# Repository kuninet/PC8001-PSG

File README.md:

# PC8001-PSG (GSX8800風PSG音源ボード)

## 概要

* PC-8001用のPSGを2個搭載したボードです。
* I/OアドレスはGSX8800風(0A0h-0A3h or 0A4h-0A7h)にしてます。

  |I/Oアドレス|説明|
  |:--|:--|
  |0A0h(0A4h)|PSG#1 レジスタ番号|
  |0A1h(0A5h)|PSG#1 データ|
  |0A2h(0A6h)|PSG#2 レジスタ番号|
  |0A3h(0A7h)|PSG#2 データ|

## 回路図

## ジャンパ設定

* I/Oアドレスを変更することが可能です。

  |JP|1-2|2-3|
  |:--|:--|:--|
  |JP1(PSG#1)|0A0h-0A1h|0A4h-0A5h|
  |JP2(PSG#2)|0A2h-0A3h|0A6h-0A7h|

## 部品表

[KiCad/PC8001-PSG.csv](KiCad/PC8001-PSG.csv)

## 参考URL

* https://piclabo.blog.ss-blog.jp/Simple8Z_PSG
  * SuperSimpleController（その２１）PSG(AY-3-8910A)の動作確認

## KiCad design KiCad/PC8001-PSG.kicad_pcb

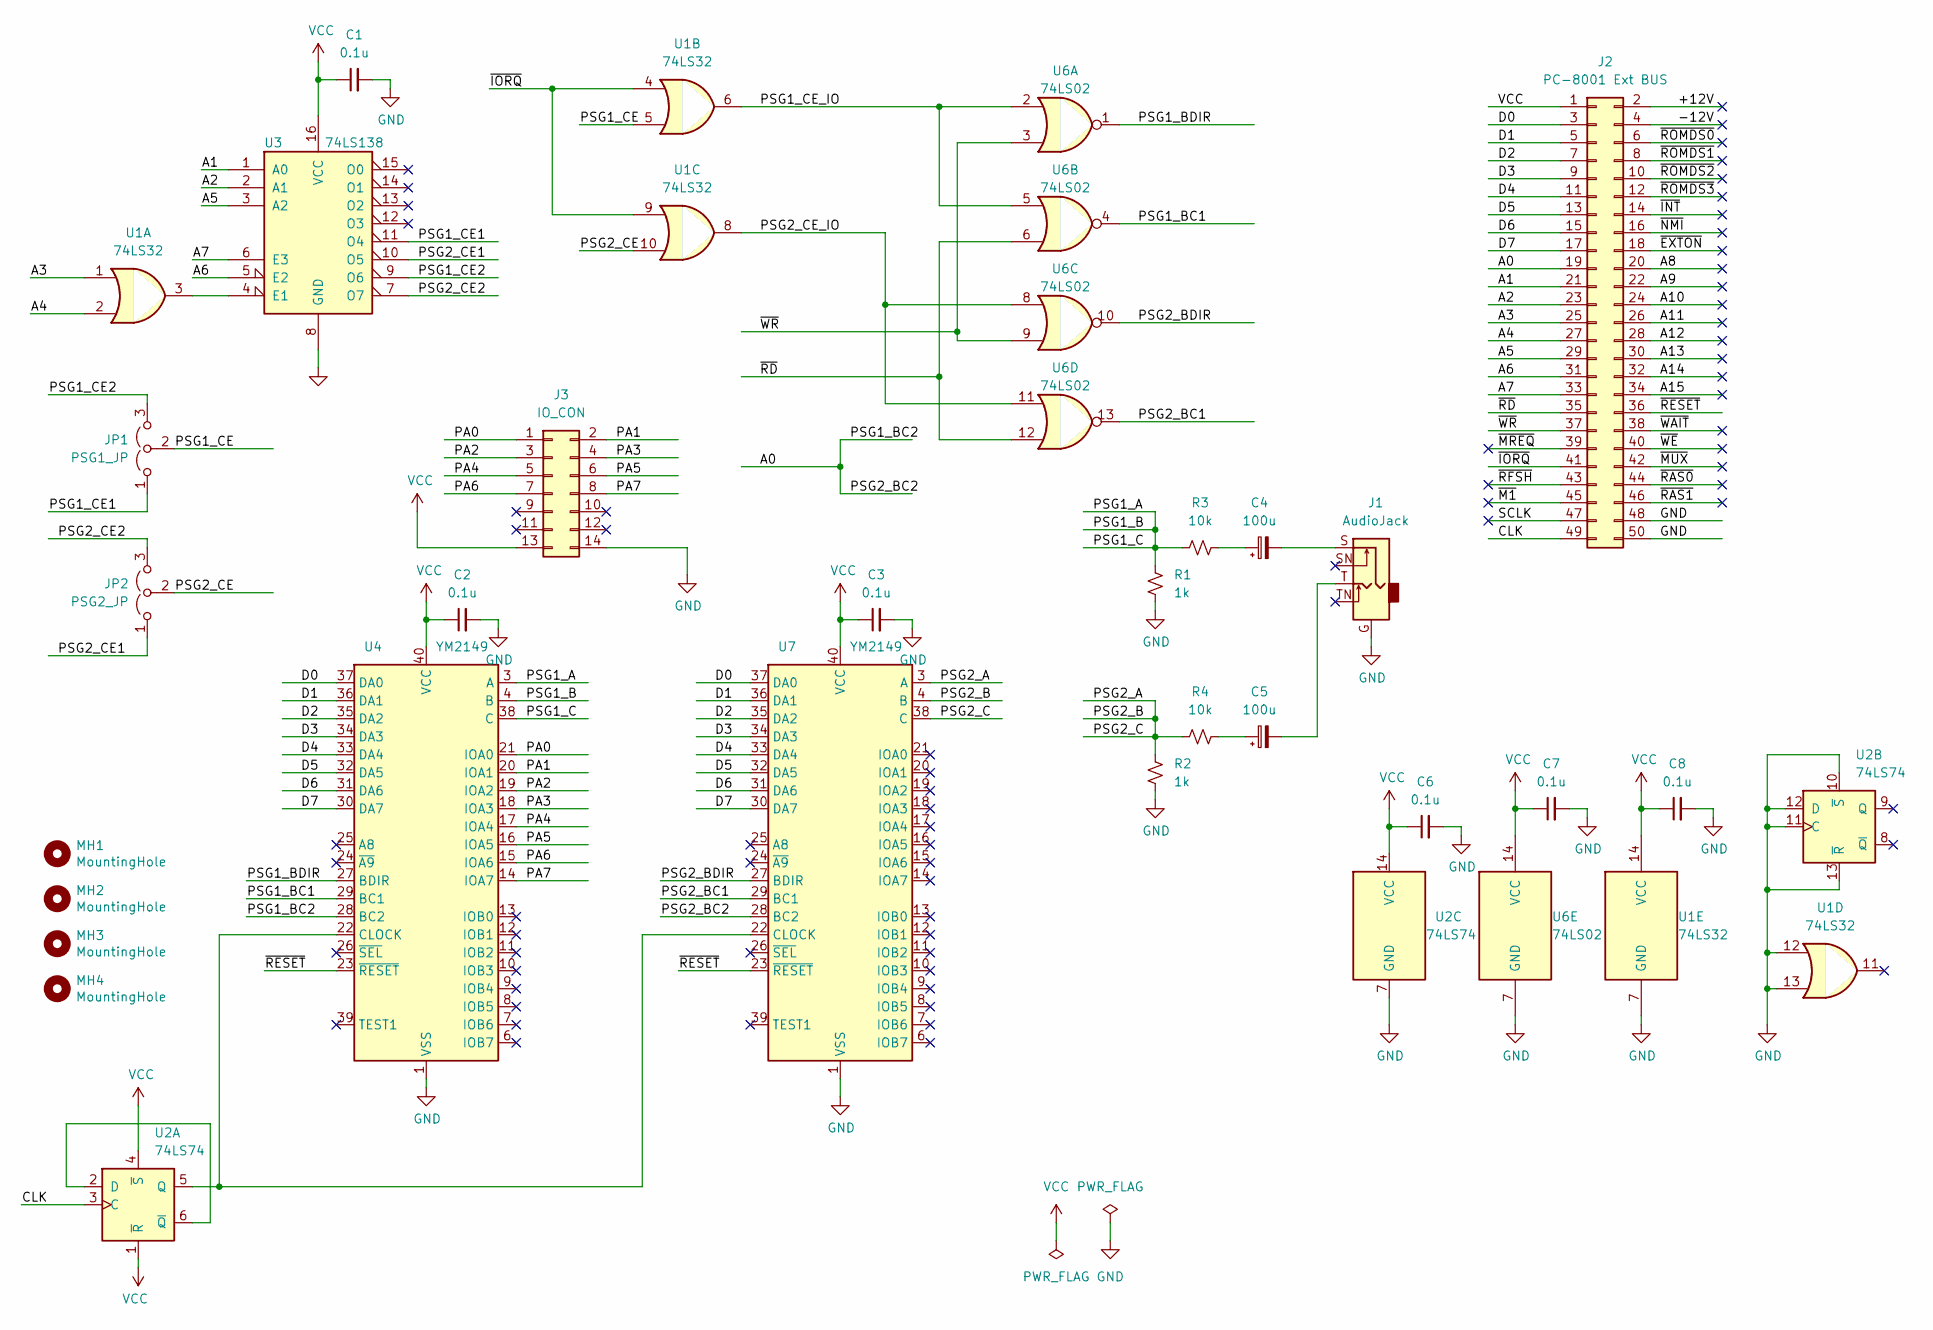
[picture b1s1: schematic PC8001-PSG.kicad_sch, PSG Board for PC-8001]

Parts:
C1, C2, C3, C6, C7, C8: 0.1u; C_Disc_D3.0mm_W1.6mm_P2.50mm
C4, C5: 100u; CP_Radial_D5.0mm_P2.50mm
J1: AudioJack; AJ-1780-2
J2: PC-8001 Ext BUS; PinHeader_2x25_P2.54mm_Horizontal
J3: IO_CON; PinHeader_2x07_P2.54mm_Vertical
JP1: PSG1_JP; PinHeader_1x03_P2.54mm_Vertical
JP2: PSG2_JP; PinHeader_1x03_P2.54mm_Vertical
MH1, MH2, MH3, MH4: MountingHole; MountingHole_3.2mm_M3
R1, R2: 1k; R_Axial_DIN0207_L6.3mm_D2.5mm_P10.16mm_Horizontal
R3, R4: 10k; R_Axial_DIN0207_L6.3mm_D2.5mm_P10.16mm_Horizontal
U1: 74LS32; DIP-14_W7.62mm_Socket
U2: 74LS74; DIP-14_W7.62mm_Socket
U3: 74LS138; DIP-16_W7.62mm_Socket
U4, U7: YM2149; DIP-40_W15.24mm
U6: 74LS02; DIP-14_W7.62mm_Socket

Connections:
/+12V: J2.2
/-12V: J2.4
/A0: J2.19, U4.28 (BC2), U7.28 (BC2)
/A1: J2.21, U3.1 (A0)
/A2: J2.23, U3.2 (A1)
/A3: J2.25, U1.1
/A4: J2.27, U1.2
/A5: J2.29, U3.3 (A2)
/A6: J2.31, U3.5 (E2)
/A7: J2.33, U3.6 (E3)
/A8: J2.20
/A9: J2.22
/A10: J2.24
/A11: J2.26
/A12: J2.28
/A13: J2.30
/A14: J2.32
/A15: J2.34
/CLK: J2.49, U2.3 (C)
/D0: J2.3, U4.37 (DA0), U7.37 (DA0)
/D1: J2.5, U4.36 (DA1), U7.36 (DA1)
/D2: J2.7, U4.35 (DA2), U7.35 (DA2)
/D3: J2.9, U4.34 (DA3), U7.34 (DA3)
/D4: J2.11, U4.33 (DA4), U7.33 (DA4)
/D5: J2.13, U4.32 (DA5), U7.32 (DA5)
/D6: J2.15, U4.31 (DA6), U7.31 (DA6)
/D7: J2.17, U4.30 (DA7), U7.30 (DA7)
/PA0: J3.1, U4.21 (IOA0)
/PA1: J3.2, U4.20 (IOA1)
/PA2: J3.3, U4.19 (IOA2)
/PA3: J3.4, U4.18 (IOA3)
/PA4: J3.5, U4.17 (IOA4)
/PA5: J3.6, U4.16 (IOA5)
/PA6: J3.7, U4.15 (IOA6)
/PA7: J3.8, U4.14 (IOA7)
/PSG1_A: R1.2, R3.1, U4.3 (A), U4.4 (B), U4.38 (C)
/PSG1_BC1: U4.29 (BC1), U6.4
/PSG1_BDIR: U4.27 (BDIR), U6.1
/PSG1_CE: JP1.2 (C), U1.5
/PSG1_CE1: JP1.1 (A), U3.11 (O4)
/PSG1_CE2: JP1.3 (B), U3.9 (O6)
/PSG1_CE_IO: U1.6, U6.2, U6.5
/PSG2_A: R2.2, R4.1, U7.3 (A), U7.4 (B), U7.38 (C)
/PSG2_BC1: U6.13, U7.29 (BC1)
/PSG2_BDIR: U6.10, U7.27 (BDIR)
/PSG2_CE: JP2.2 (C), U1.10
/PSG2_CE1: JP2.1 (A), U3.10 (O5)
/PSG2_CE2: JP2.3 (B), U3.7 (O7)
/PSG2_CE_IO: U1.8, U6.8, U6.11
/SCLK: J2.47
/~EXTON: J2.18
/~INT: J2.14
/~IORQ: J2.41, U1.4, U1.9
/~M1: J2.45
/~MREQ: J2.39
/~MUX: J2.42
/~NMI: J2.16
/~RAS0: J2.44
/~RAS1: J2.46
/~RD: J2.35, U6.6, U6.12
/~RESET: J2.36, U4.23 (~RESET), U7.23 (~RESET)
/~RFSH: J2.43
/~ROMDS0: J2.6
/~ROMDS1: J2.8
/~ROMDS2: J2.10
/~ROMDS3: J2.12
/~WAIT: J2.38
/~WE: J2.40
/~WR: J2.37, U6.3, U6.9
GND: C1.2, C2.2, C3.2, C6.2, C7.2, C8.2, J1.G, J2.48, J2.50, J3.14, R1.1, R2.1, U1.7 (GND), U1.12, U1.13, U2.7 (GND), U2.10 (~S), U2.11 (C), U2.12 (D), U2.13 (~R), U3.8 (GND), U4.1 (VSS), U6.7 (GND), U7.1 (VSS)
unnamed: C4.1, R3.2
unnamed: C4.2, J1.S
unnamed: C5.1, R4.2
unnamed: C5.2, J1.T
unnamed: U2.2 (D), U2.6 (~Q)
unnamed: U2.5 (Q), U4.22 (CLOCK), U7.22 (CLOCK)
unnamed: U1.3, U3.4 (E1)
VCC: C1.1, C2.1, C3.1, C6.1, C7.1, C8.1, J2.1, J3.13, U1.14 (VCC), U2.1 (~R), U2.4 (~S), U2.14 (VCC), U3.16 (VCC), U4.40 (VCC), U6.14 (VCC), U7.40 (VCC)

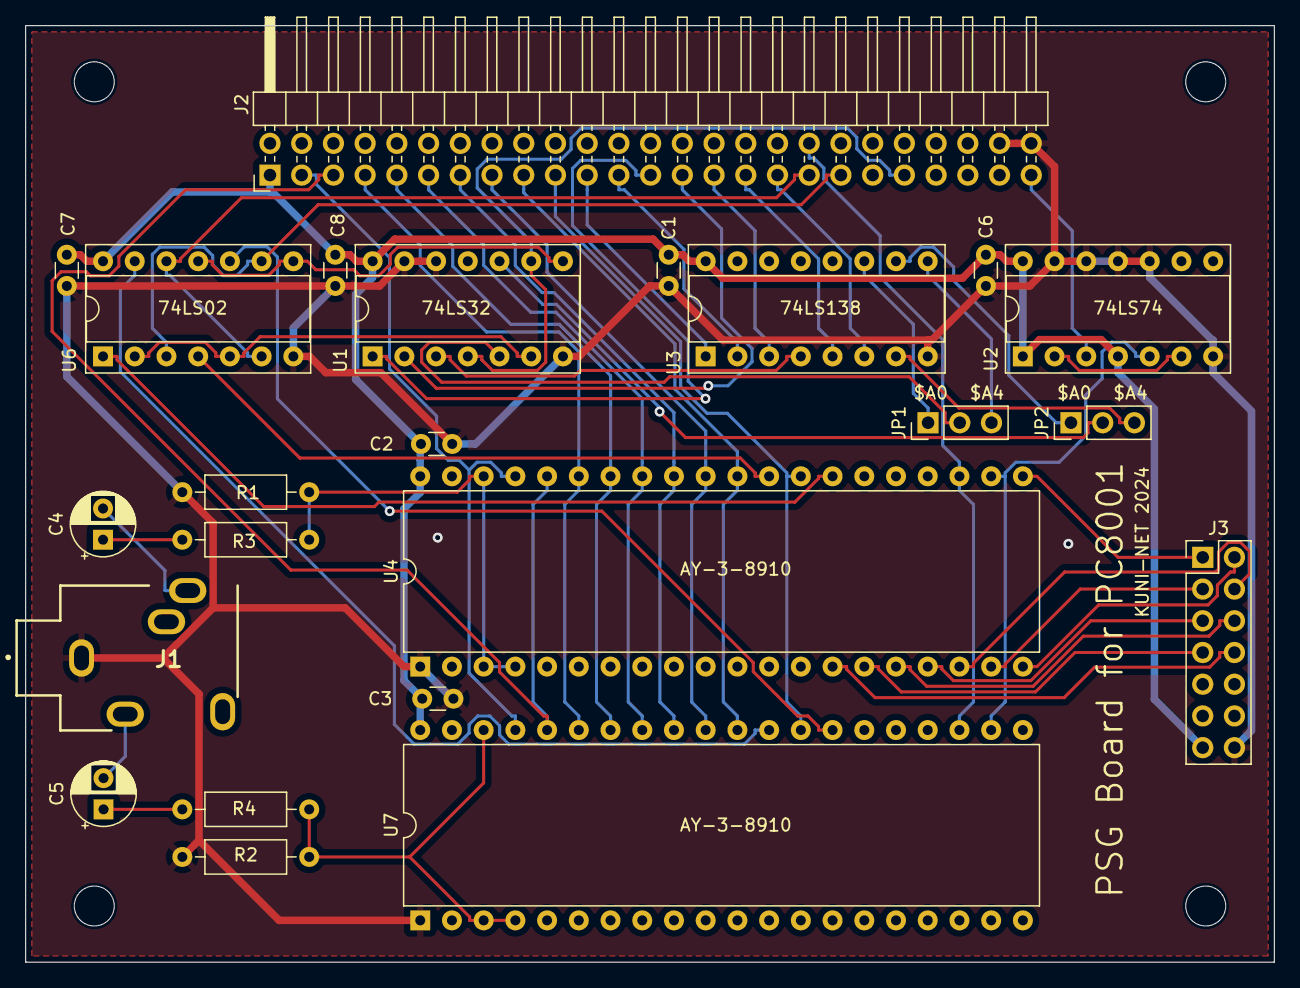
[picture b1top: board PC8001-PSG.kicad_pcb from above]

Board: 2 copper layers, 100.0 x 75.0 mm, 27 parts (0 on the bottom side), 52 nets.

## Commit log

2023-12-23 回路図初版
2024-01-03 プリントパターン等検討、ガーバー出力
2024-01-04 AJ-1780フットプリント修正 & ガーバーデータ再出力
2024-02-12 部品表追加、README更新
